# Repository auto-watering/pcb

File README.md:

# Auto Watering PCB

KiCad project for auto watering PCB.
This PCB is designed for up to 6 valves.

This KiCad project requires Espressif KiCad Library.

You can find a firmware designed to run on this board [on the dedicated repository](https://github.com/auto-watering/firmware).

## Required parts

- ESP32 DevKit C
- Support for ESP32 board
- For each valve:
  - SRD12VDC relay
  - EL817(D)-G or PC817 C photocoupler
  - LED
  - JST connector 1x02 2.50mm pitch (for case mounted LED)
  - 1 kOhm resistor
  - 56 Ohm resistor
  - flyback diode
  - TerminalBlock Phoenix MKDS-1,5/2 1x02 5mm pitch (for valve)
  - Valves themselves (for example RainBird HV series, 24VAC)
- 5V DC power supply for ESP32
- 12V DC power supply for relays command
- Power supply for valves (24VAC for RainBird HV series)
- 3x TerminalBlock Phoenix MKDS-1,5/2 1x02 5mm pitch (for power supplies)

## Prototyping

Thanks to [PCBWay](https://www.pcbway.com) for helping prototyping this project
by sending me assembled boards !
The build quality is great, and their manufacturing service was very available
and professional to help me to prepare everything and create the bill of
material (BOM).

Below are some pictures of these prototypes boards.

You can find in the project releases all [PCBWay](https://www.pcbway.com)
related resources to make it (gerbers, positions, BOM).

It is perfectly working, installed in a waterproof case, with power supplies
for 5VDC, 12VDC, 24VAC, and the ESP32 with the
[firmware](https://github.com/auto-watering/firmware).

## Improvements

As EL817(D)-G optocoupler should be OK to control the relay coil, it may be
appropriate to use a MOFSET between them.

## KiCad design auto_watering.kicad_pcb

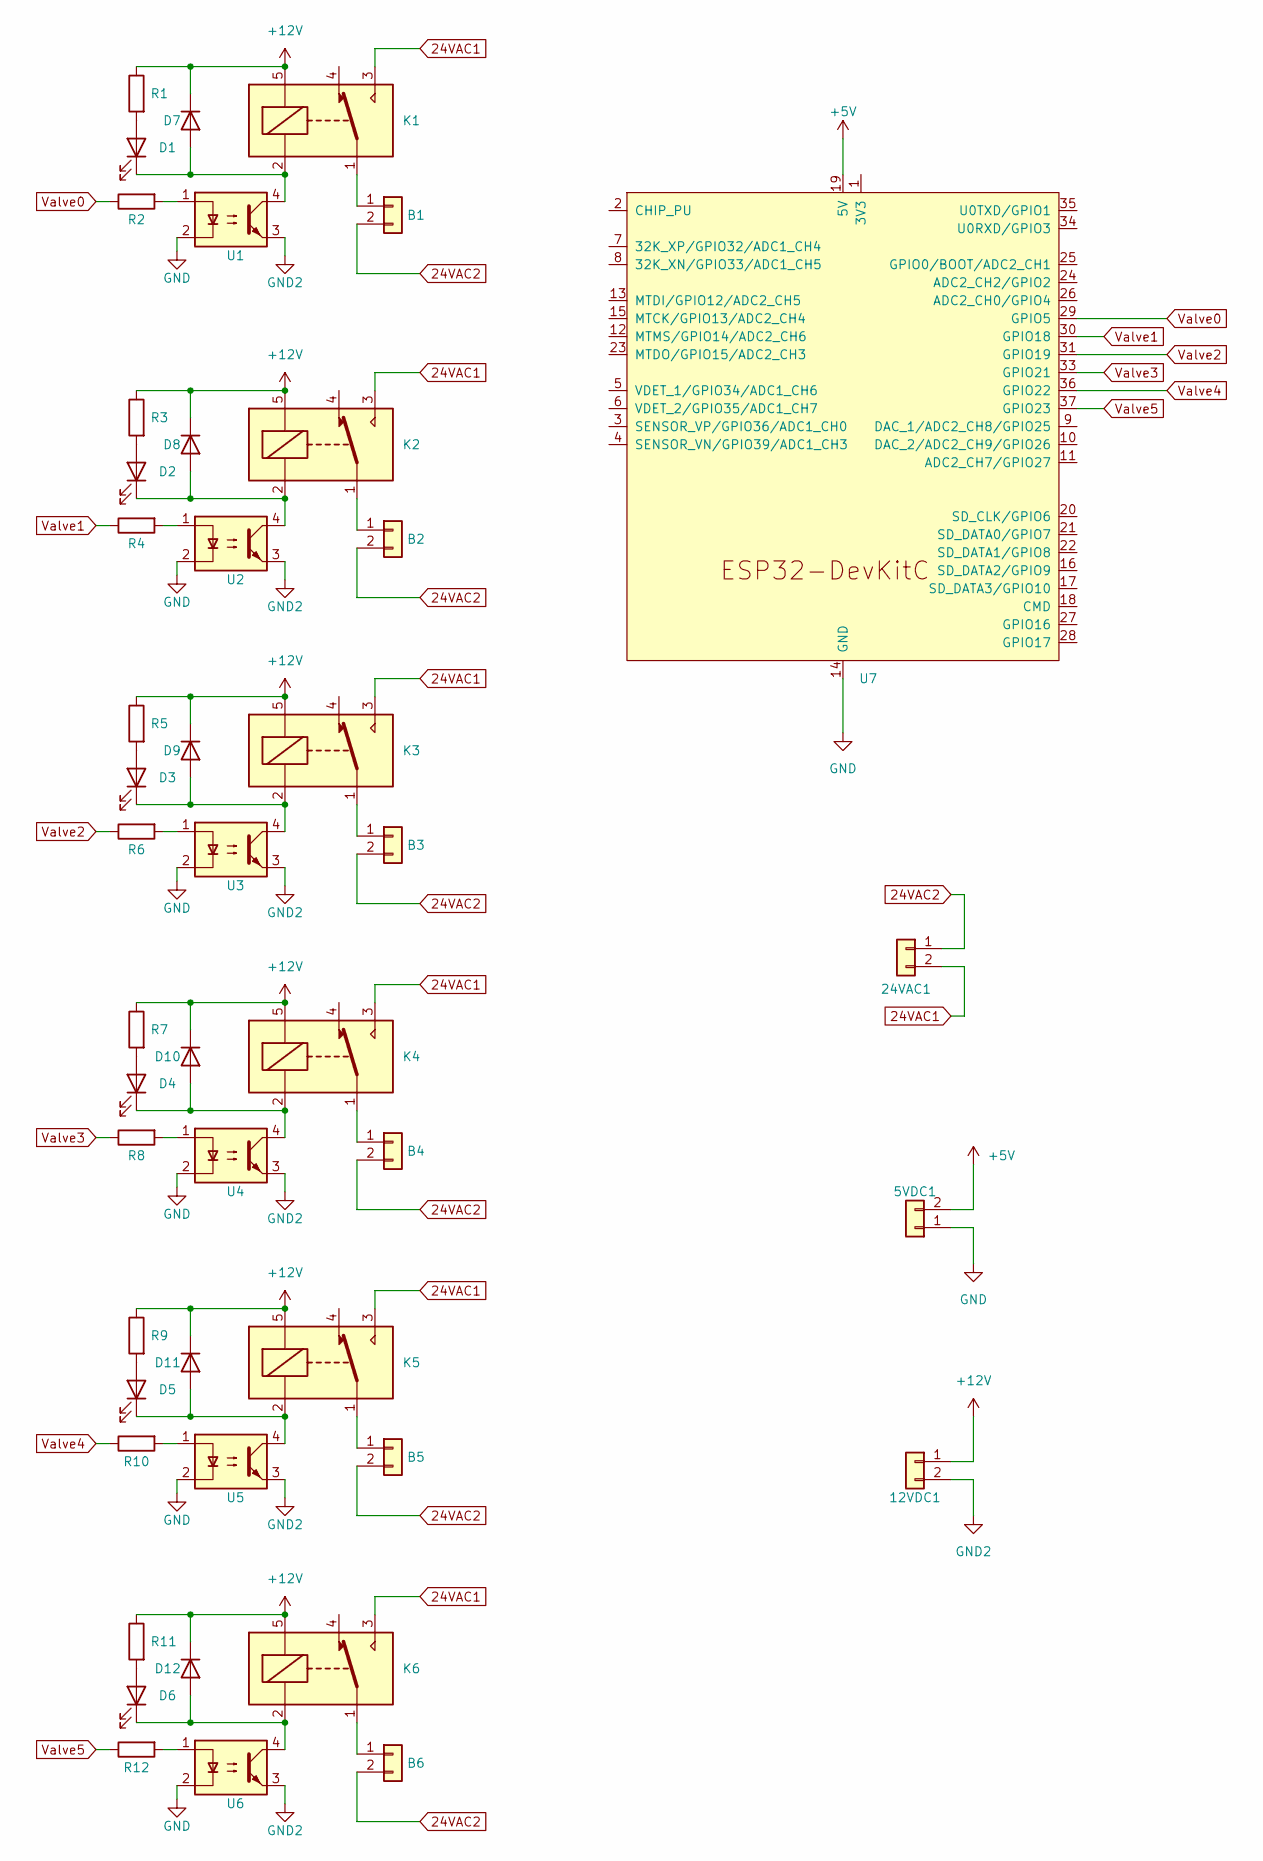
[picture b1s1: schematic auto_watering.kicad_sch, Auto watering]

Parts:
5VDC1, 12VDC1, 24VAC1: Conn_01x02; TerminalBlock_Phoenix_MKDS-1,5-2_1x02_P5.00mm_Horizontal
B1, B2, B3, B4, B5, B6: Conn_01x02; TerminalBlock_Phoenix_MKDS-1,5-2_1x02_P5.00mm_Horizontal
D1, D2, D3, D4, D5, D6: LED; JST_XH_B2B-XH-A_1x02_P2.50mm_Vertical
D7, D8, D9, D10, D11, D12: 1N4004; D_DO-41_SOD81_P10.16mm_Horizontal
K1, K2, K3, K4, K5, K6: SRD12VDC; Relay_SPDT_SANYOU_SRD_Series_Form_C
R1, R3, R5, R7, R9, R11: 1K; R_Axial_DIN0207_L6.3mm_D2.5mm_P10.16mm_Horizontal
R2, R4, R6, R8, R10, R12: 56; R_Axial_DIN0207_L6.3mm_D2.5mm_P10.16mm_Horizontal
U1, U2, U3, U4, U5, U6: PC817; DIP-4_W7.62mm
U7: ESP32-DevKitC

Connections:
24VAC1: 24VAC1.2, K1.3, K2.3, K3.3, K4.3, K5.3, K6.3
24VAC2: 24VAC1.1, B1.2, B2.2, B3.2, B4.2, B5.2, B6.2
+5V: 5VDC1.2, U7.19 (5V)
+12V: 12VDC1.1, D7.1 (K), D8.1 (K), D9.1 (K), D10.1 (K), D11.1 (K), D12.1 (K), K1.5, K2.5, K3.5, K4.5, K5.5, K6.5, R1.1, R3.1, R5.1, R7.1, R9.1, R11.1
GND: 5VDC1.1, U1.2, U2.2, U3.2, U4.2, U5.2, U6.2, U7.14 (GND), U7.32 (GND), U7.38 (GND)
GND2: 12VDC1.2, U1.3, U2.3, U3.3, U4.3, U5.3, U6.3
unnamed: B1.1, K1.1
unnamed: B2.1, K2.1
unnamed: B3.1, K3.1
unnamed: B4.1, K4.1
unnamed: B5.1, K5.1
unnamed: B6.1, K6.1
unnamed: D1.2 (A), R1.2
unnamed: D1.1 (K), D7.2 (A), K1.2, U1.4
unnamed: D2.2 (A), R3.2
unnamed: D2.1 (K), D8.2 (A), K2.2, U2.4
unnamed: D3.2 (A), R5.2
unnamed: D3.1 (K), D9.2 (A), K3.2, U3.4
unnamed: D4.2 (A), R7.2
unnamed: D5.2 (A), R9.2
unnamed: D6.2 (A), R11.2
unnamed: D4.1 (K), D10.2 (A), K4.2, U4.4
unnamed: D5.1 (K), D11.2 (A), K5.2, U5.4
unnamed: D6.1 (K), D12.2 (A), K6.2, U6.4
unnamed: R2.2, U1.1
unnamed: R4.2, U2.1
unnamed: R6.2, U3.1
unnamed: R8.2, U4.1
unnamed: R10.2, U5.1
unnamed: R12.2, U6.1
Valve0: R2.1, U7.29 (GPIO5)
Valve1: R4.1, U7.30 (GPIO18)
Valve2: R6.1, U7.31 (GPIO19)
Valve3: R8.1, U7.33 (GPIO21)
Valve4: R10.1, U7.36 (GPIO22)
Valve5: R12.1, U7.37 (GPIO23)

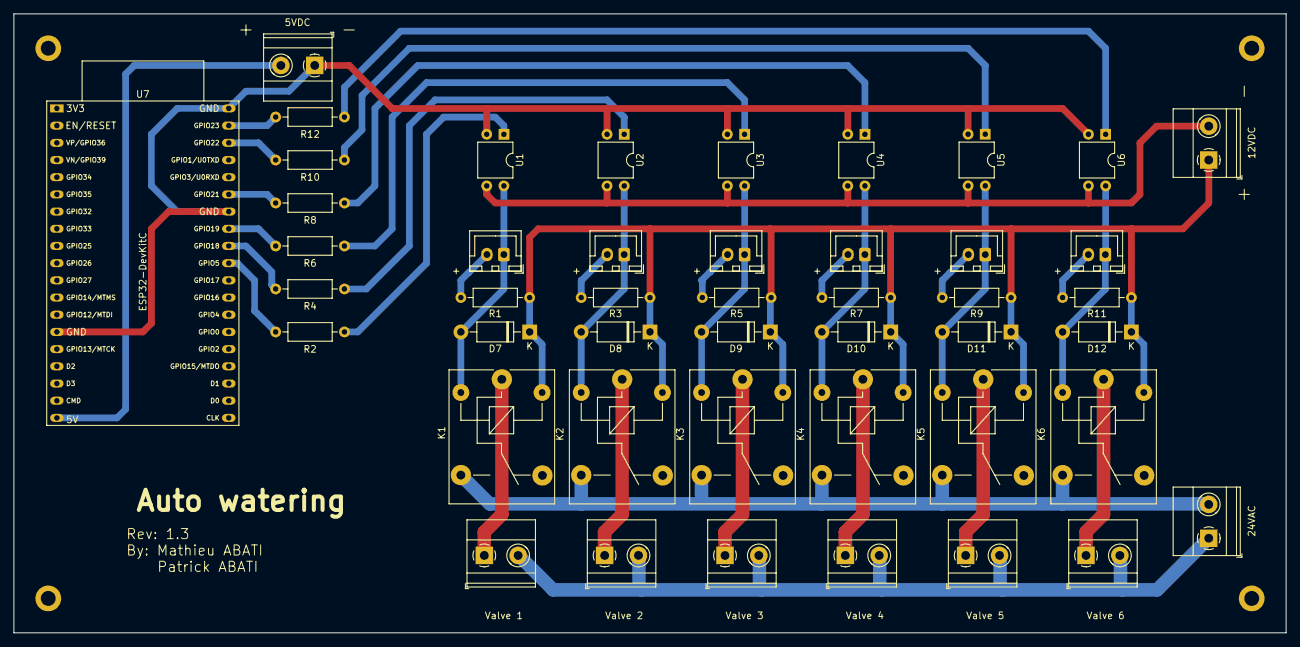
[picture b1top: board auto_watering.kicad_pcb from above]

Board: 2 copper layers, 188.0 x 91.4 mm, 46 parts (0 on the bottom side), 36 nets.

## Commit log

2025-08-09 Release KiCad files
2025-08-09 Add PCB 3D view picture
2025-08-11 Update README to add link to firmware
2025-09-04 Update README and add pictures
2025-09-05 Add remark about optocoupler and relay coil control
2025-09-06 Add photocoupler reference used in PCBWay BOM
2025-09-06 Remove JLC marking on PCB
2025-09-06 Fix typo
